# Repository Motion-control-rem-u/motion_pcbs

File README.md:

# motion_pcbs
Contiene los archivos esquematicos y layout de las PCB manufacturadas en el 2022  y las que van a ser manufacturadas en el 2023.

## Autores:
### Sebastian Guyacan Mesa 

### Laura Valentina Lara Perez

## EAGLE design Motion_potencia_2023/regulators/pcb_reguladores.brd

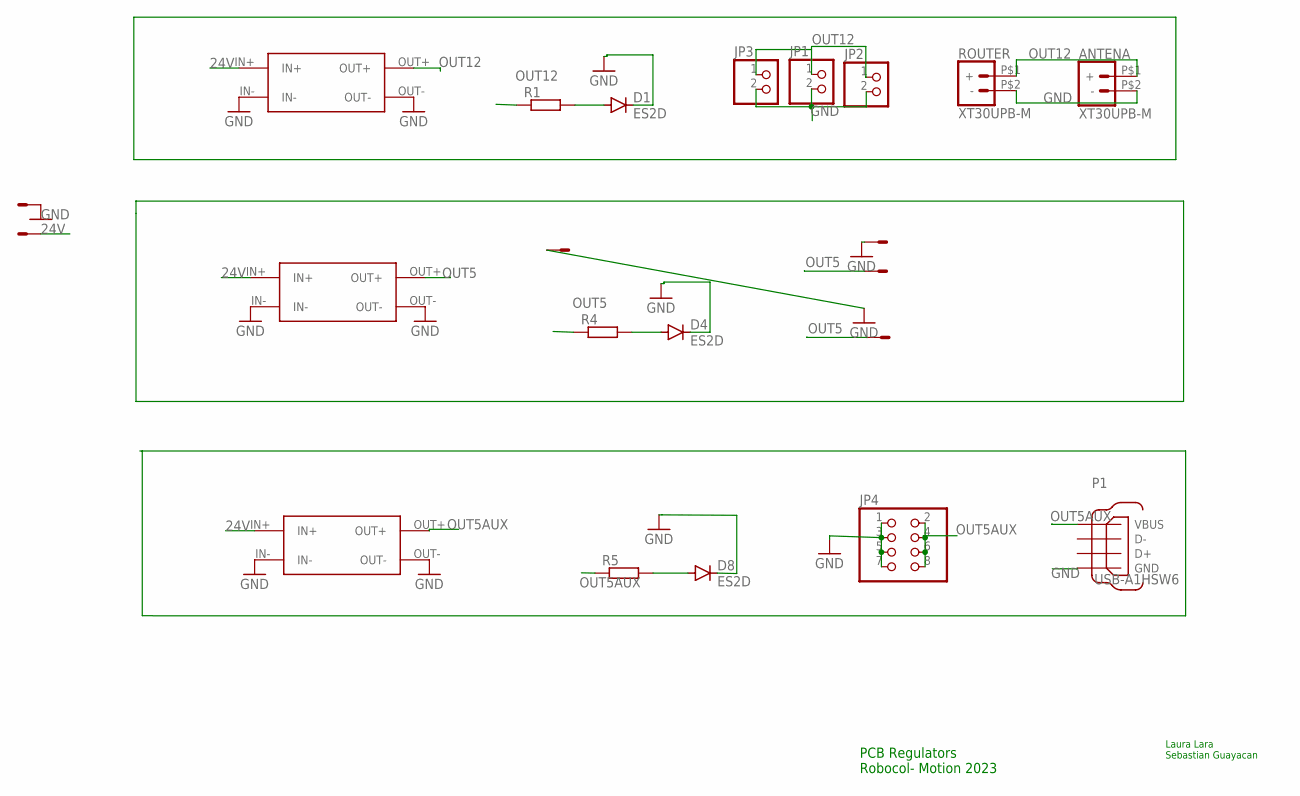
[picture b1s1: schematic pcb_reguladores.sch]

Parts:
ANTENA: XT30UPB-M
D1, D4, D8: ES2D; SMB
JP1, JP2, JP3: PINHD-1X2; 1X02
JP4: PINHD-2X4; 2X04
P1: USB-A1HSW6; OST_USB-A1HSW6
R1, R4, R5: SMK
REG5AUX, REG5V, REG12V: XL4015_5A; XL4015_PADS
ROUTER: XT30UPB-M
V_IN: 5566-25569-2; 5569-2
X1, X3: 5566-25569-2; 5569-2

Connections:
24V: REG5AUX.IN+, REG5V.IN+, REG12V.IN+, V_IN.2
GND: ANTENA.P$2 (-), D1.C, D4.C, D8.C, JP4.1, JP4.3, JP4.5, JP4.7, P1.4 (GND), REG5AUX.IN-, REG5AUX.OUT-, REG5V.IN-, REG5V.OUT-, REG12V.IN-, REG12V.OUT-, ROUTER.P$2 (-), V_IN.1, X1.1, X3.1
unnamed: JP1.2, JP2.2, JP3.2
unnamed: D4.A, R4.1
unnamed: D1.A, R1.1
unnamed: D8.A, R5.1
OUT5: R4.2, REG5V.OUT+, X1.2, X3.2
OUT5AUX: JP4.2, JP4.4, JP4.6, JP4.8, P1.1 (VBUS), R5.2, REG5AUX.OUT+
OUT12: ANTENA.P$1 (+), JP1.1, JP2.1, JP3.1, R1.2, REG12V.OUT+, ROUTER.P$1 (+)

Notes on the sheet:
PCB Regulators Robocol- Motion 2023
Laura Lara Sebastian Guayacan

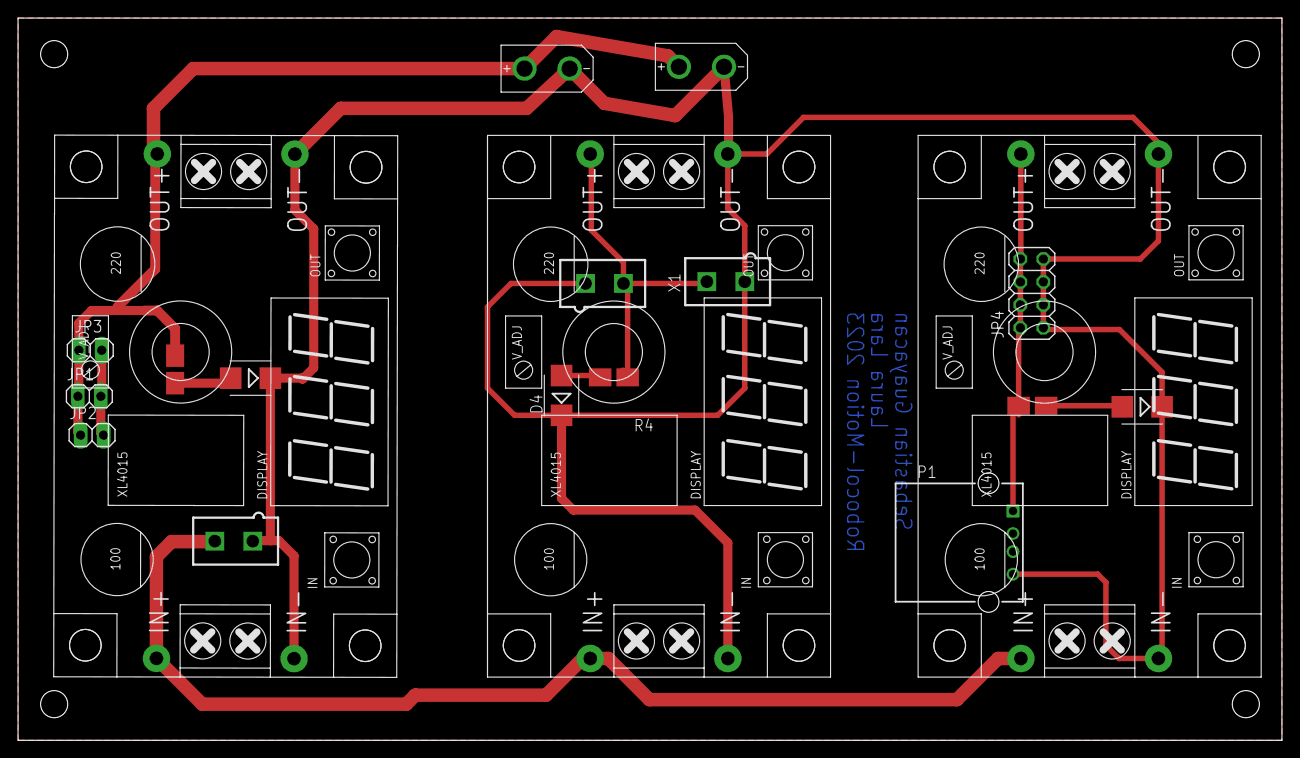
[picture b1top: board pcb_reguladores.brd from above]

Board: 2 copper layers, 140.0 x 80.0 mm, 19 parts (0 on the bottom side), 9 nets.

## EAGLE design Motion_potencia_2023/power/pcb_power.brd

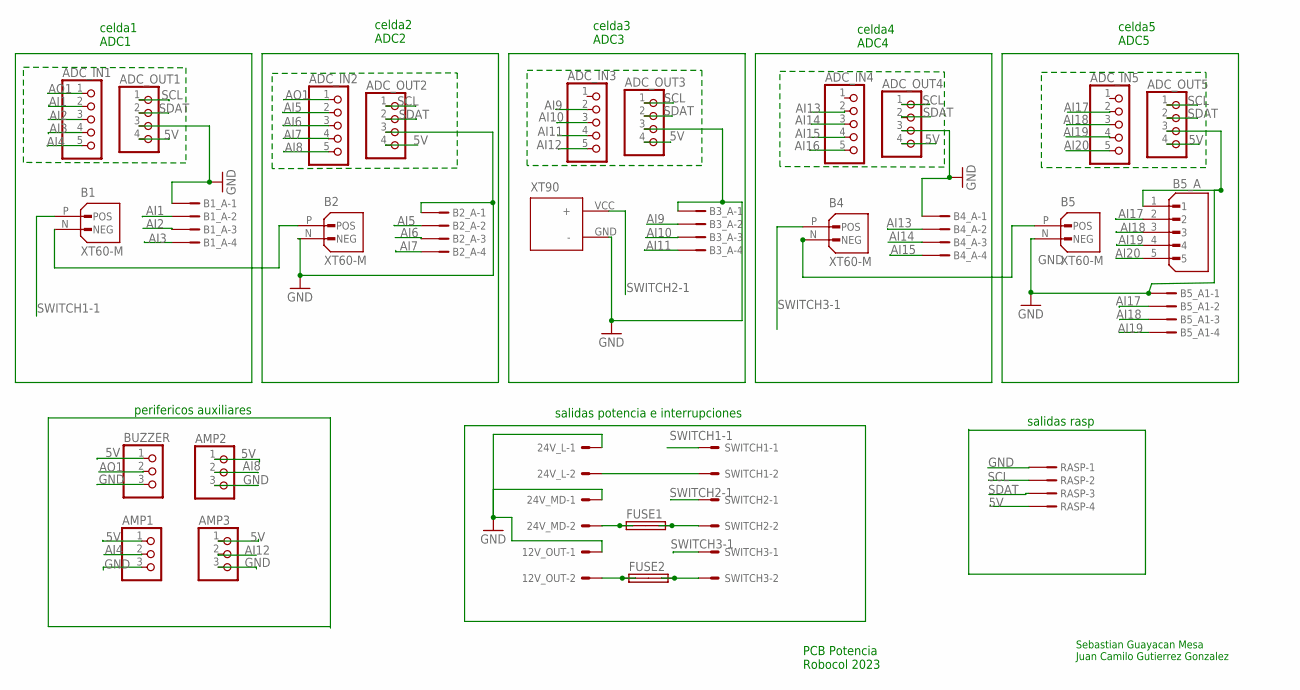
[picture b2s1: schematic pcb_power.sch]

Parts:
12V_OUT, 24V_L, 24V_MD: 5566-25569-2; 5569-2
ADC_IN1, ADC_IN2, ADC_IN3, ADC_IN4, ADC_IN5: PINHD-1X5; 1X05
ADC_OUT1, ADC_OUT2, ADC_OUT3, ADC_OUT4, ADC_OUT5: PINHD-1X4; 1X04
AMP1, AMP2, AMP3: PINHD-1X3; 1X03
B1, B2, B4, B5: XT60-M; AMASS_XT60-M
B1_A, B2_A, B3_A, B4_A, B5_A1: B4B-ZR
B3: XT90; XT90_PADS
B5_A: B5B-ZR(LF)(SN); JST_B5B-ZR(LF)(SN)
BUZZER: PINHD-1X3; 1X03
FUSE1, FUSE2: SHK20L
RASP: B4B-ZR
SWITCH1, SWITCH2, SWITCH3: 5566-25569-2; 5569-2

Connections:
5V: ADC_OUT1.4, ADC_OUT2.4, ADC_OUT3.4, ADC_OUT4.4, ADC_OUT5.4, AMP1.1, AMP2.1, AMP3.1, BUZZER.1, RASP.4
AI1: ADC_IN1.2, B1_A.2
AI2: ADC_IN1.3, B1_A.3
AI3: ADC_IN1.4, B1_A.4
AI4: ADC_IN1.5, AMP1.2
AI5: ADC_IN2.2, B2_A.2
AI6: ADC_IN2.3, B2_A.3
AI7: ADC_IN2.4, B2_A.4
AI8: ADC_IN2.5, AMP2.2
AI9: ADC_IN3.2, B3_A.2
AI10: ADC_IN3.3, B3_A.3
AI11: ADC_IN3.4, B3_A.4
AI12: ADC_IN3.5, AMP3.2
AI13: ADC_IN4.2, B4_A.2
AI14: ADC_IN4.3, B4_A.3
AI15: ADC_IN4.4, B4_A.4
AI16: ADC_IN4.5
AI17: ADC_IN5.2, B5_A.2, B5_A1.2
AI18: ADC_IN5.3, B5_A.3, B5_A1.3
AI19: ADC_IN5.4, B5_A.4, B5_A1.4
AI20: ADC_IN5.5, B5_A.5
AO1: ADC_IN1.1, ADC_IN2.1, BUZZER.2
GND: 12V_OUT.1, 24V_L.1, 24V_MD.1, ADC_OUT1.3, ADC_OUT2.3, ADC_OUT3.3, ADC_OUT4.3, ADC_OUT5.3, AMP1.3, AMP2.3, AMP3.3, B1_A.1, B2.N (NEG), B2_A.1, B3.GND (-), B3_A.1, B4_A.1, B5.N (NEG), B5_A.1, B5_A1.1, BUZZER.3, RASP.1
unnamed: 24V_MD.2, FUSE1.1A, FUSE1.1B
unnamed: FUSE1.2A, FUSE1.2B, SWITCH2.2
unnamed: 12V_OUT.2, FUSE2.1A, FUSE2.1B
unnamed: FUSE2.2A, FUSE2.2B, SWITCH3.2
unnamed: 24V_L.2, SWITCH1.2
unnamed: B1.N (NEG), B2.P (POS)
unnamed: B4.N (NEG), B5.P (POS)
SCL: ADC_OUT1.1, ADC_OUT2.1, ADC_OUT3.1, ADC_OUT4.1, ADC_OUT5.1, RASP.2
SDAT: ADC_OUT1.2, ADC_OUT2.2, ADC_OUT3.2, ADC_OUT4.2, ADC_OUT5.2, RASP.3
SWITCH1-1: B1.P (POS), SWITCH1.1
SWITCH2-1: B3.VCC (+), SWITCH2.1
SWITCH3-1: B4.P (POS), SWITCH3.1

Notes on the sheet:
PCB Potencia Robocol 2023
Sebastian Guayacan Mesa Juan Camilo Gutierrez Gonzalez
salidas rasp
salidas potencia e interrupciones
perifericos auxiliares
celda1 ADC1
celda2 ADC2
celda3 ADC3
celda4 ADC4
celda5 ADC5

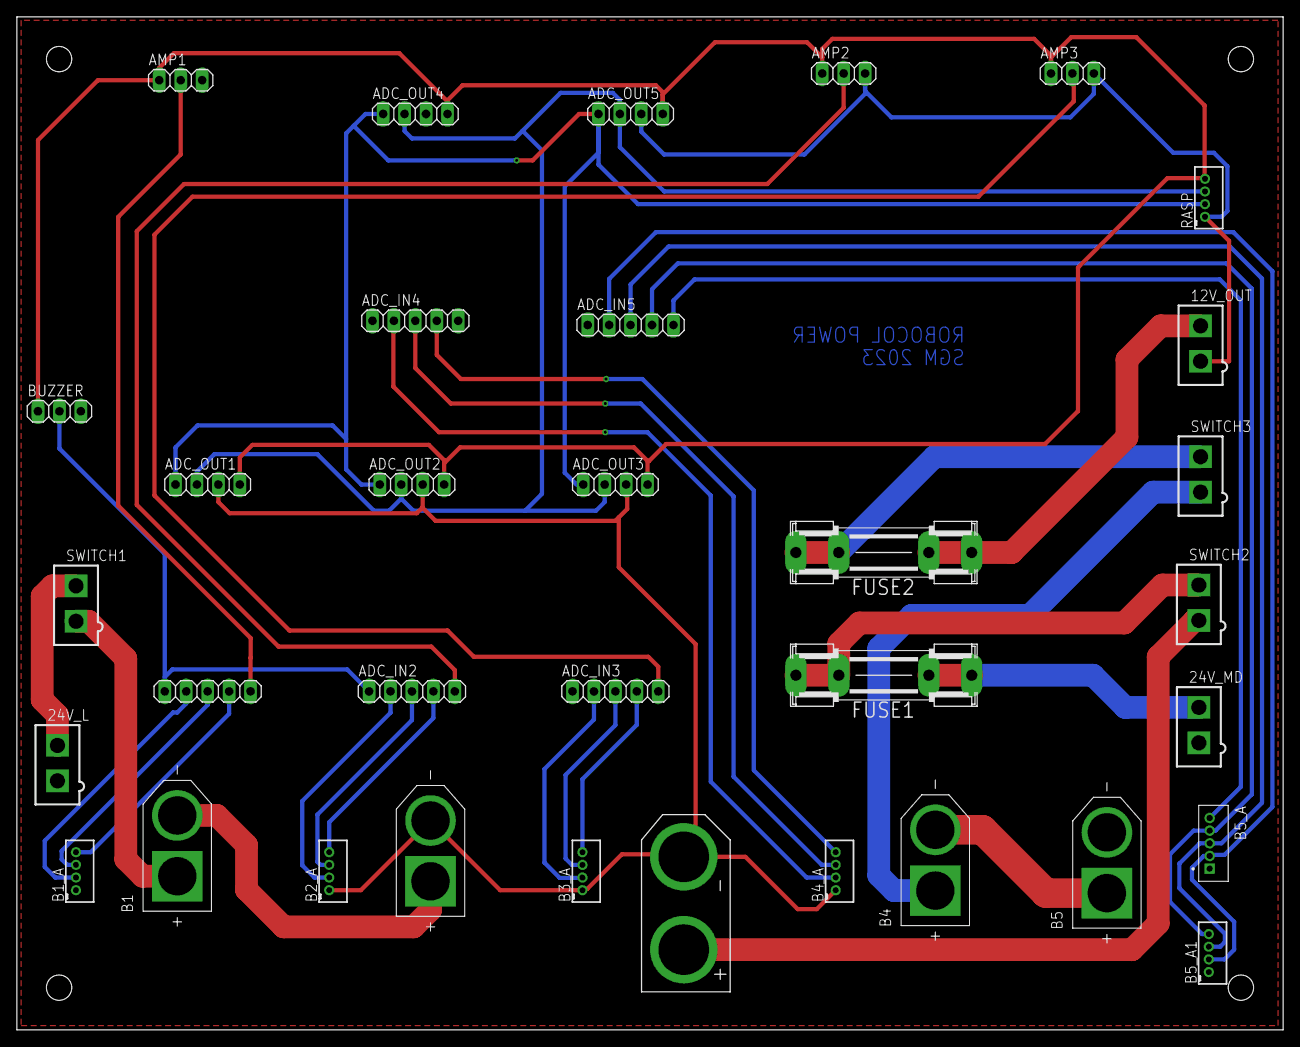
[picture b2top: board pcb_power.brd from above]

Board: 2 copper layers, 150.0 x 120.0 mm, 34 parts (0 on the bottom side), 34 nets.

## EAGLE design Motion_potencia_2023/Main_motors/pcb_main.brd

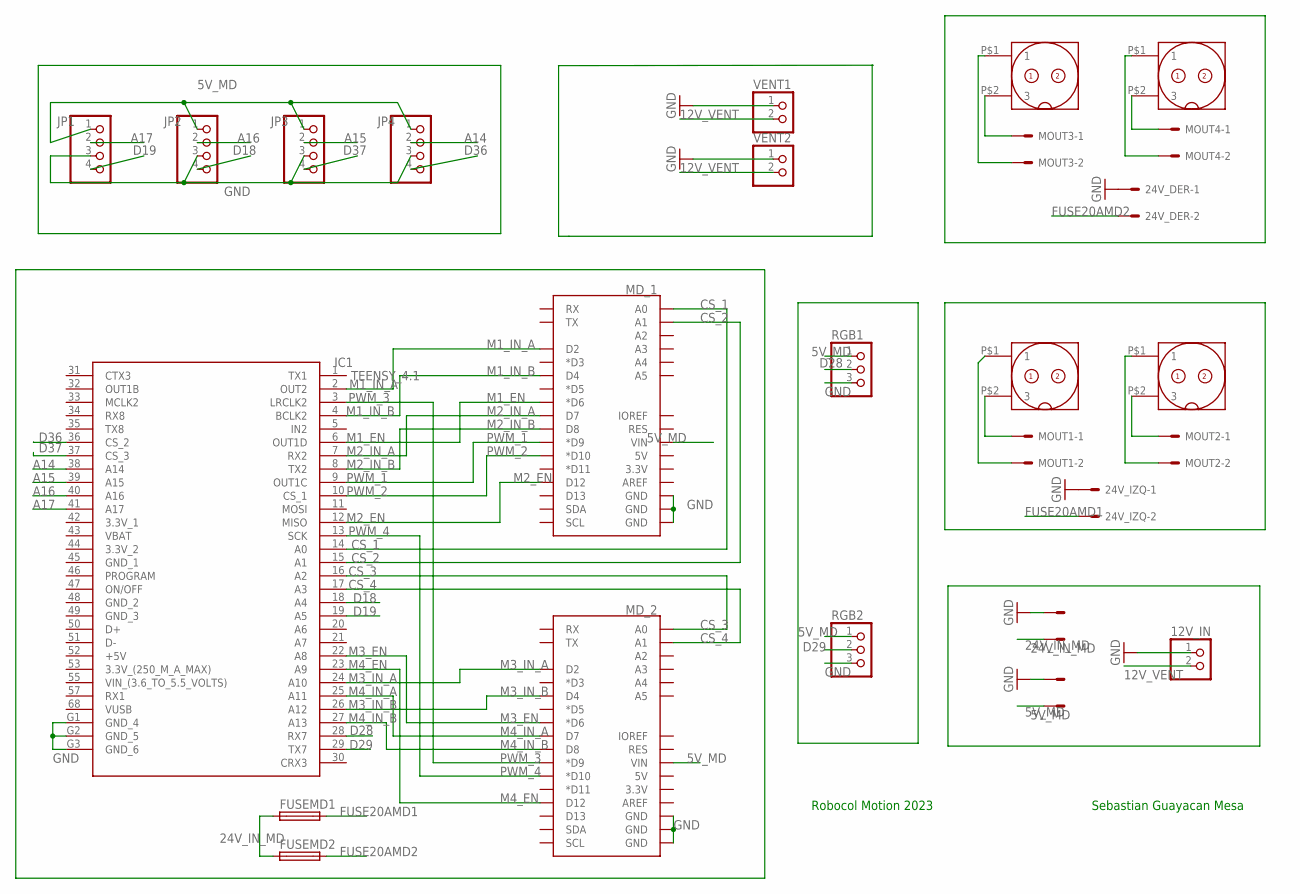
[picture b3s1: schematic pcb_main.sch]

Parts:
5_MD, 24V_DER, 24V_IZQ, 24V_MD: 5566-25569-2; 5569-2
12V_IN: PINHD-1X2; 1X02
FUSEMD1, FUSEMD2: FUSEBLANK_5X20MM; FUSE_HOLDER_5X20MM
IC1: TEENSY_4.1; TEENSY41
JP1, JP2, JP3, JP4: PINHD-1X4; 1X04
M1, M2, M3, M4: GX16_2_PINS; GX16_2_PINS_PADS
MD_1, MD_2: ARDUINO_UNO_R3_SHIELDBASIC; UNO_R3_SHIELD
MOUT1, MOUT2, MOUT3, MOUT4: 5566-25569-2; 5569-2
RGB1, RGB2: PINHD-1X3; 1X03
VENT1, VENT2: PINHD-1X2; 1X02

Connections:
5V_MD: 5_MD.2, JP1.1, JP2.1, JP3.1, JP4.1, MD_1.VIN, MD_2.VIN, RGB1.1, RGB2.1
12V_VENT: 12V_IN.2, VENT1.2, VENT2.2
24V_IN_MD: 24V_MD.2, FUSEMD1.1, FUSEMD2.1
A14: IC1.38 (A14), JP4.2
A15: IC1.39 (A15), JP3.2
A16: IC1.40 (A16), JP2.2
A17: IC1.41 (A17), JP1.2
CS_1: IC1.14 (A0), MD_1.A0
CS_2: IC1.15 (A1), MD_1.A1
CS_3: IC1.16 (A2), MD_2.A0
CS_4: IC1.17 (A3), MD_2.A1
D18: IC1.18 (A4), JP2.4
D19: IC1.19 (A5), JP1.4
D28: IC1.28 (RX7), RGB1.2
D29: IC1.29 (TX7), RGB2.2
D36: IC1.36 (CS_2), JP4.4
D37: IC1.37 (CS_3), JP3.4
FUSE20AMD1: 24V_IZQ.2, FUSEMD1.2
FUSE20AMD2: 24V_DER.2, FUSEMD2.2
GND: 5_MD.1, 12V_IN.1, 24V_DER.1, 24V_IZQ.1, 24V_MD.1, IC1.G1 (GND_4), IC1.G2 (GND_5), IC1.G3 (GND_6), JP1.3, JP2.3, JP3.3, JP4.3, MD_1.GND@0 (GND), MD_1.GND@1 (GND), MD_1.GND@2 (GND), MD_2.GND@0 (GND), MD_2.GND@1 (GND), MD_2.GND@2 (GND), RGB1.3, RGB2.3, VENT1.1, VENT2.1
M1_EN: IC1.6 (OUT1D), MD_1.D6 (*D6)
M1_IN_A: IC1.2 (OUT2), MD_1.D2
M1_IN_B: IC1.4 (BCLK2), MD_1.D4
M2_EN: IC1.12 (MISO), MD_1.D12
M2_IN_A: IC1.7 (RX2), MD_1.D7
M2_IN_B: IC1.8 (TX2), MD_1.D8
M3_EN: IC1.22 (A8), MD_2.D6 (*D6)
M3_IN_A: IC1.24 (A10), MD_2.D2
M3_IN_B: IC1.26 (A12), MD_2.D4
M4_EN: IC1.23 (A9), MD_2.D12
M4_IN_A: IC1.25 (A11), MD_2.D7
M4_IN_B: IC1.27 (A13), MD_2.D8
unnamed: M1.P$2 (3), MOUT1.1
unnamed: M2.P$2 (3), MOUT2.1
unnamed: M2.P$1 (1), MOUT2.2
unnamed: M1.P$1 (1), MOUT1.2
unnamed: M4.P$2 (3), MOUT4.1
unnamed: M4.P$1 (1), MOUT4.2
unnamed: M3.P$2 (3), MOUT3.1
unnamed: M3.P$1 (1), MOUT3.2
PWM_1: IC1.9 (OUT1C), MD_1.D9 (*D9)
PWM_2: IC1.10 (CS_1), MD_1.D10 (*D10)
PWM_3: IC1.3 (LRCLK2), MD_2.D9 (*D9)
PWM_4: IC1.13 (SCK), MD_2.D10 (*D10)

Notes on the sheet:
Robocol Motion 2023
Sebastian Guayacan Mesa

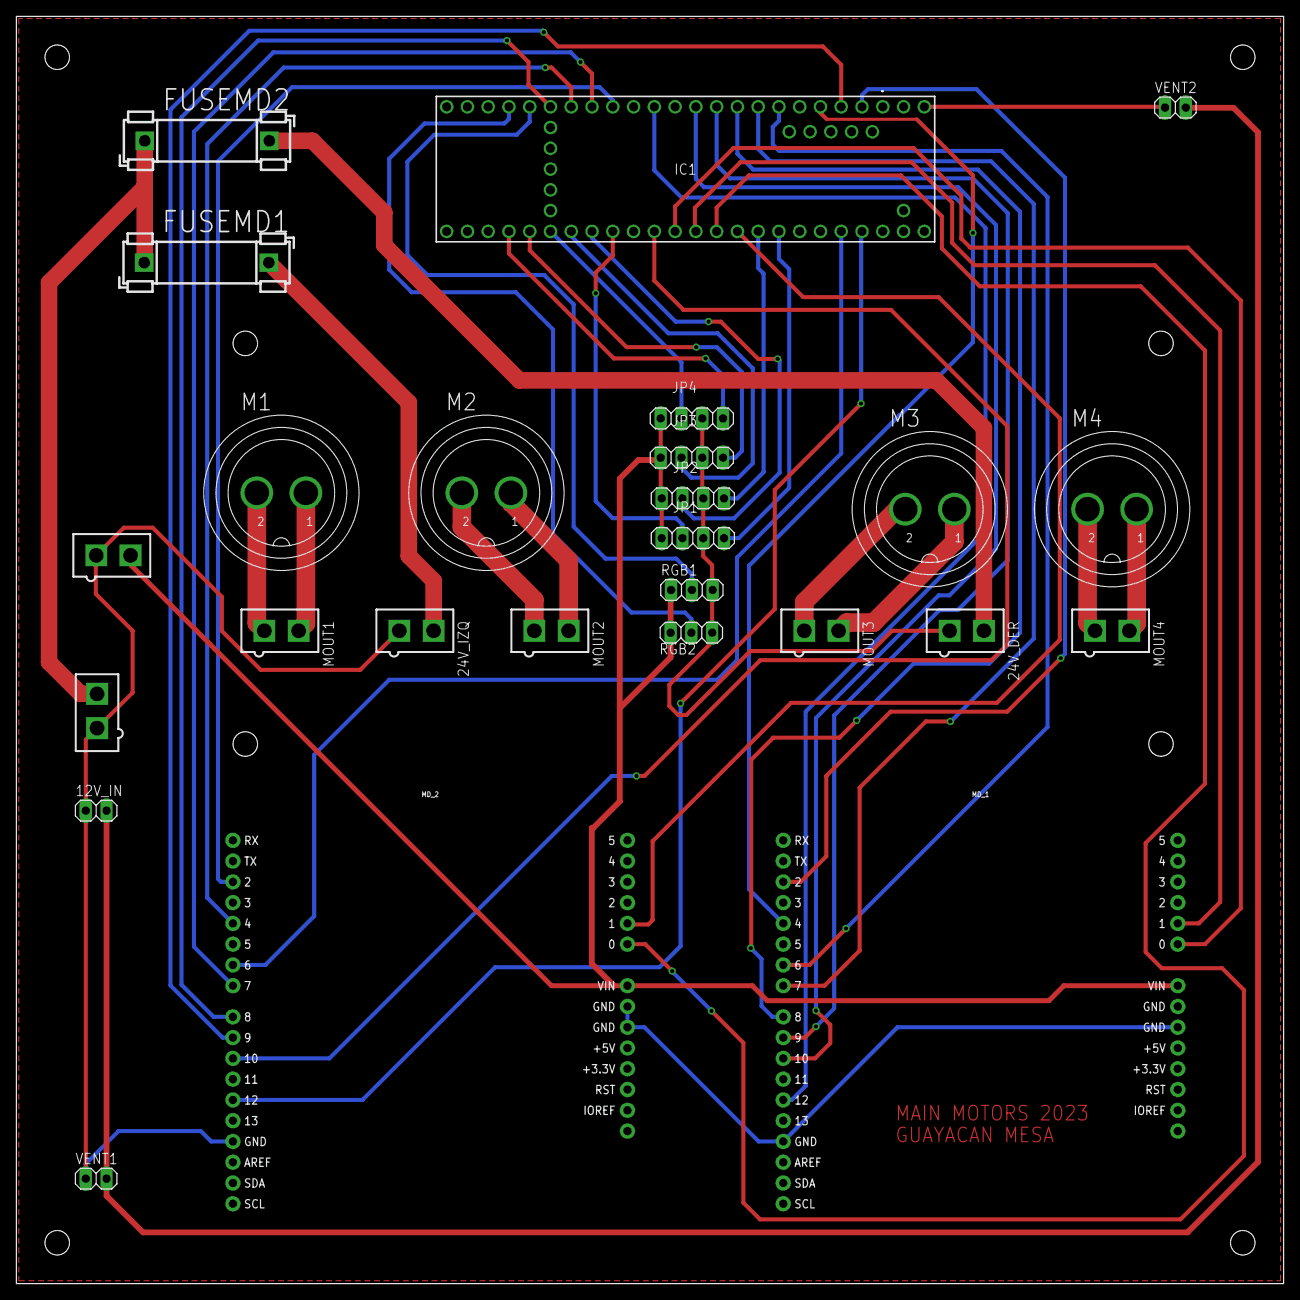
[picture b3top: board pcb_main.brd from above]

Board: 2 copper layers, 155.0 x 155.0 mm, 26 parts (0 on the bottom side), 44 nets.

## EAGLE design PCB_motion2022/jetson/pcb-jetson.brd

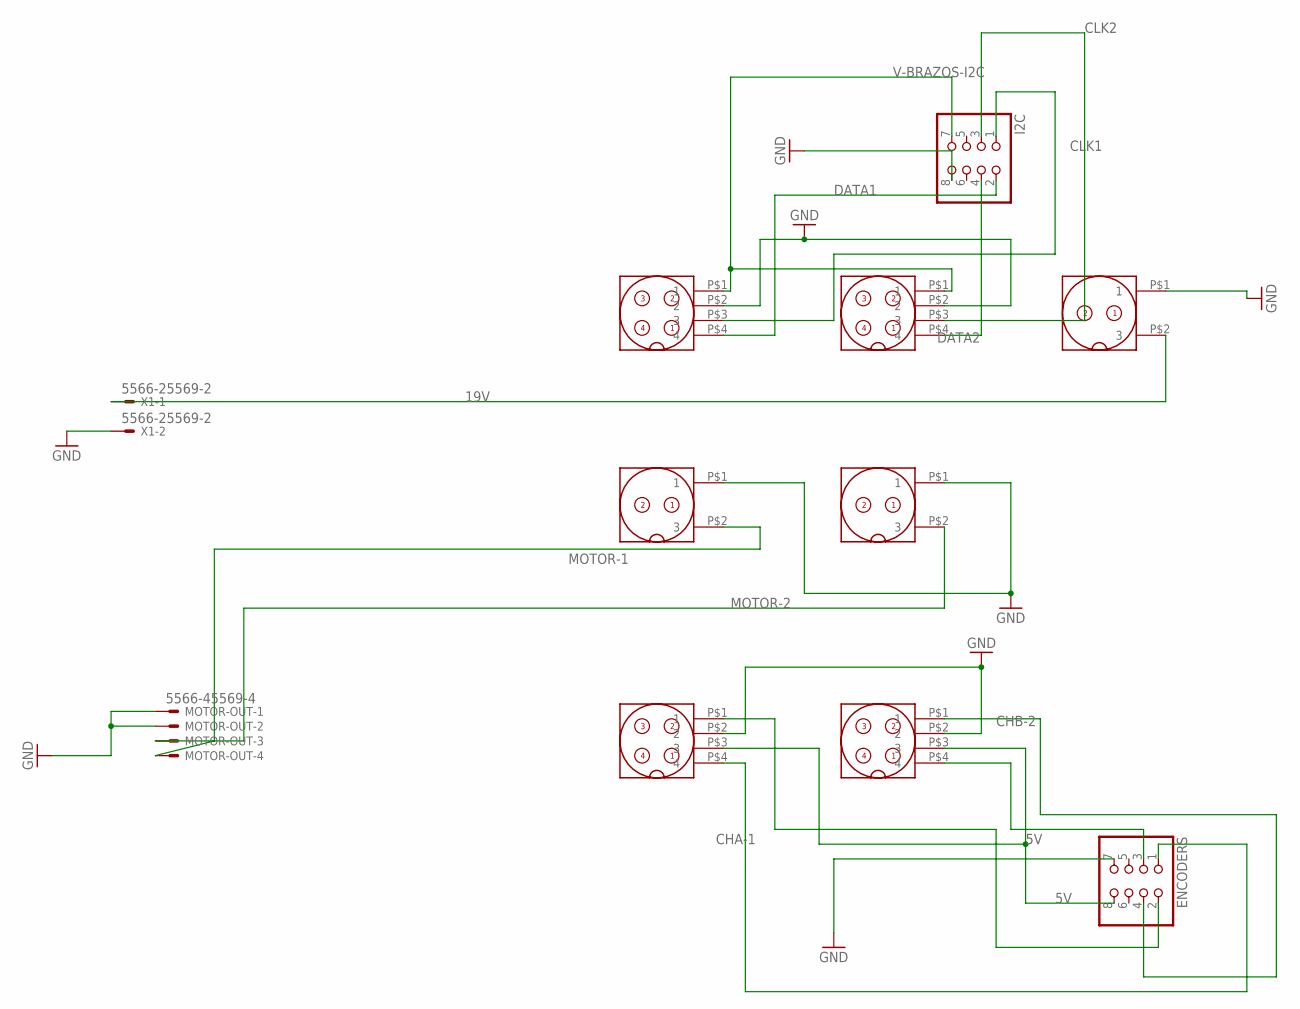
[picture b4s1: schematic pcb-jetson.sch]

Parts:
BRAZO-I2C-2: GX16_4_PINS; GX16_4_PINS_PADS
BRAZO_I2C-1: GX16_4_PINS; GX16_4_PINS_PADS
ENCODERS: PINHD-2X4; 2X04
I2C: PINHD-2X4; 2X04
JETSONIN: GX16_2_PINS; GX16_2_PINS_PADS
MOTOR1, MOTOR2: GX16_2_PINS; GX16_2_PINS_PADS
MOTOR-OUT: 5566-45569-4; 5569-4
U$3, U$4: GX16_4_PINS; GX16_4_PINS_PADS
X1: 5566-25569-2; 5569-2

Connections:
5V: ENCODERS.8, U$3.P$3 (3), U$4.P$3 (3)
19V: JETSONIN.P$2 (3), X1.1
CHA-1: ENCODERS.1, U$3.P$4 (4)
CHA-2: ENCODERS.3, U$4.P$4 (4)
CHB-1: ENCODERS.2, U$3.P$1 (1)
CHB-2: ENCODERS.4, U$4.P$1 (1)
CLK1: BRAZO_I2C-1.P$3 (3), I2C.1
CLK2: BRAZO-I2C-2.P$3 (3), I2C.3
DATA1: BRAZO_I2C-1.P$4 (4), I2C.2
DATA2: BRAZO-I2C-2.P$4 (4), I2C.4
GND: BRAZO-I2C-2.P$2 (2), BRAZO_I2C-1.P$2 (2), ENCODERS.7, I2C.8, JETSONIN.P$1 (1), MOTOR1.P$1 (1), MOTOR2.P$1 (1), MOTOR-OUT.1, MOTOR-OUT.2, U$3.P$2 (2), U$4.P$2 (2), X1.2
MOTOR-1: MOTOR1.P$2 (3), MOTOR-OUT.4
MOTOR-2: MOTOR2.P$2 (3), MOTOR-OUT.3
V-BRAZOS-I2C: BRAZO-I2C-2.P$1 (1), BRAZO_I2C-1.P$1 (1), I2C.7

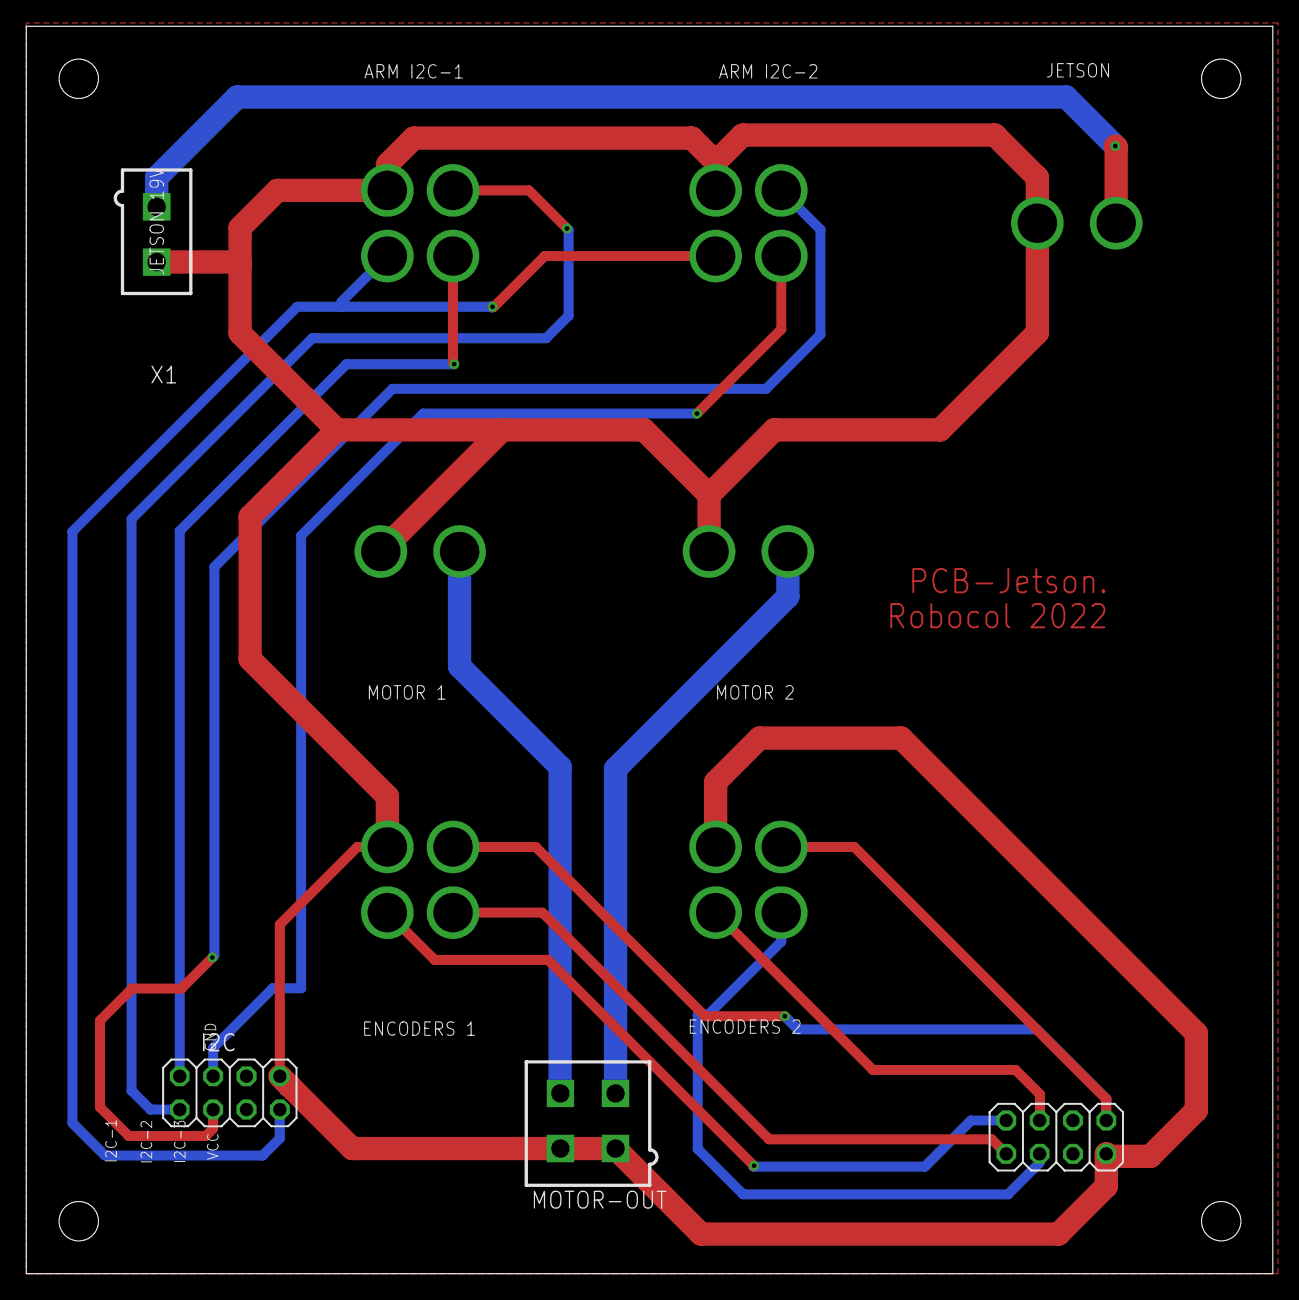
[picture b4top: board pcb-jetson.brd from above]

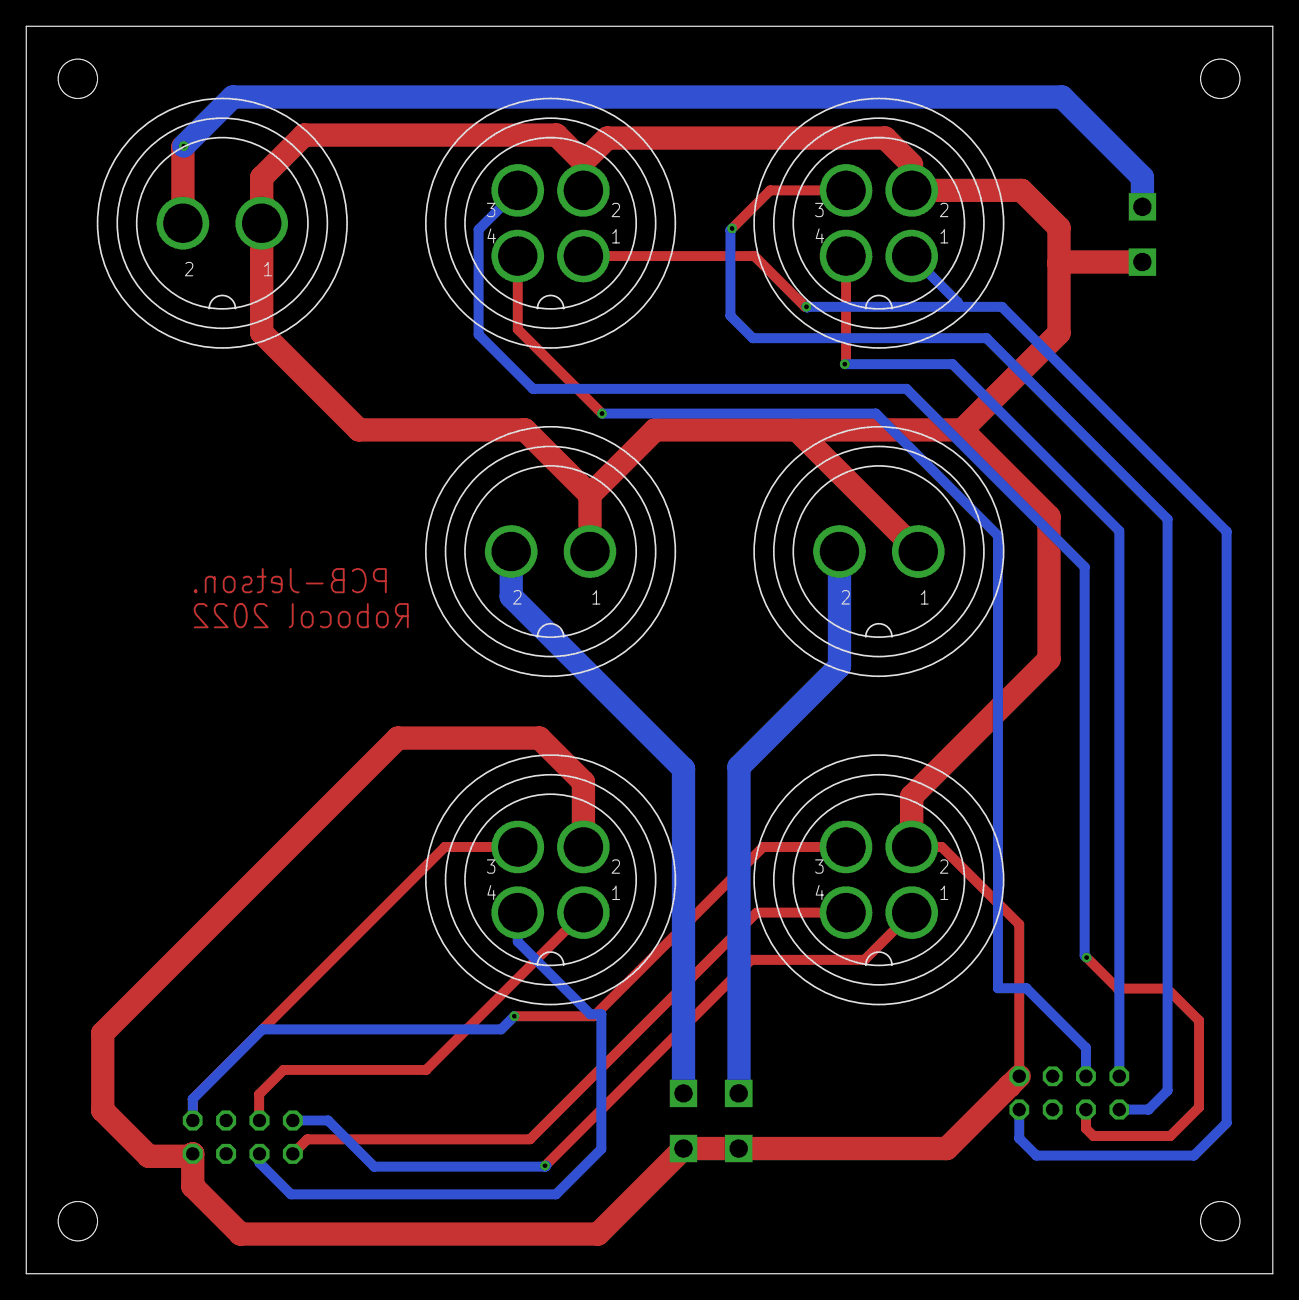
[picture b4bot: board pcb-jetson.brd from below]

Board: 2 copper layers, 94.9 x 95.0 mm, 11 parts (7 on the bottom side), 14 nets.

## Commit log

2023-02-09 incluimos los autores
2023-02-09 Se agregan los archivos del 2022
2023-02-21 Se crean los esquemáticos y boardas de algunas PCBs que se van a fabircar en el 2023, esquematico reguladores lista
2023-02-23 main lista, sin revisión
2023-03-10 main, power
2023-03-13 PCBs mandadas a fabricar
2023-08-24 BOM's

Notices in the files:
parts and their libraries:
SparkFun-Boards: Licensing: Creative Commons ShareAlike 4.0 International - https://creativecommons.org/licenses/by-sa/4.0
